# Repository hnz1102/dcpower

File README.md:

<div align="center">
  <h1><code>DC Power Unit for Breadboard</code></h1>
  
</div>

# DC Power Unit for Breadboard

This is a DC Power Unit for Breadboard based on ESP32-S3 microcontroller and AP33772S USB Power Delivery (PD) Sink Controller. It can supply power to the breadboard from USB Power Delivery (PD) Charger with support for both Standard Power Range (SPR) and Extended Power Range (EPR) modes. The output voltage can be controlled from 0v to 20V in SPR mode and up to 28V(*1) in EPR mode with step of 10mV.   
There are 2 types of adopters for the output terminal: Single positive power output terminal and dual positive/negative output terminal. It is easy to connect to the breadboard with standard 2.54mm pitch pin header. If you select the dual positive/negative output terminal adopter, the output voltage can be halved by positive and negative voltage. E.g. If you set the output voltage to 20V, you can get +10V and -10V from the positive and negative output terminal.

***1: Maximum voltage is limited to 28V by AP33772S hardware specifications. Some PD chargers may not support EPR mode or only support up to 16V/5A. Please check your PD charger specifications.**

The left image shows the single positive output terminal adopter, and the right image shows the dual positive/negative output terminal adopter.

## Key Features

- **High Power Delivery**: Up to 100W from USB PD Charger
- **Multiple Voltage Outputs**: 0V to 20V in SPR mode, 0V to 28V in EPR mode (10mV steps)
- **High Current Support**: Up to 5A when PD Charger supports EPR, but some chargers support up to 90% of the maximum current.
- **Touch Control Interface**: Front panel touch switch for voltage selection and output control
- **Precise Control**: PID controller maintains constant output voltage
- **High Accuracy Monitoring and Control**: 10mV voltage accuracy using shunt resistor and INA228 current sensor, with 1mV resolution.
- **Real-time Display**: OLED display shows voltage, current, power consumption, and temperature
- **Data Logging**: WiFi connectivity for sending measurement data to InfluxDB server
- **Web Dashboard**: Data visualization using InfluxDB dashboard
- **Safety Features**: Over Voltage Protection (OVP), Under Voltage Protection (UVP), Over Current Protection (OCP). Over Temperature Protection (OTP) does not implemented.

****Note**: If you use 21V or higher voltage, input voltage is 28v or higher, and differential voltage is over 3V and output current is over 3A, the MOSFET device is in the high consumption state and the unit temperature may rise over 80 degrees Celsius. Please be careful about the temperature. You can set the maximum temperature in the configuration file. The default value is 80 degrees Celsius. If the temperature exceeds the limit, the output will be disabled automatically. I recommend using less than 0.7A current at 21V or higher voltage. Otherwise, if you set the output voltage to 27V or higher, the temperature rise is not a problem.**

****Note**: This unit uses a micro controller and a USB PD controller. These controllers need the power to operate. Therefore, if you use a over current, the power source may be shut down by the over current protection of the PD charger. In this case, This unit cannot operate and will be turned off. Please use the current within the specification of your PD charger.**

## Hardware Components

- **ESP32-S3-WROOM-1-N16R8**: Main microcontroller
- **AP33772S**: USB Power Delivery Sink Controller with EPR support
- **INA228**: High-precision current/voltage sensor
- **SSD1331**: Color OLED display (96x64 pixels)
- **Touch Interface**: Capacitive touch sensors for user interaction
- **MOSFET Load Circuit**: Electronic load for testing and regulation

## Software Architecture

The firmware is written in Rust using the ESP-IDF framework and consists of several modules:

- `main.rs`: Main application logic and system initialization
- `usbpd.rs`: AP33772S USB-PD driver interface using the ap33772s-driver crate
- `displayctl.rs`: OLED display control and user interface
- `currentlogs.rs`: Current and voltage measurement using INA228
- `touchpad.rs`: Touch sensor interface and user input handling
- `pidcont.rs`: PID controller for voltage regulation
- `wifi.rs`: WiFi connectivity and network management
- `transfer.rs`: Data transmission to InfluxDB server
- `syslogger.rs`: System logging functionality

ap33772s-driver crate is used for USB-PD communication with the AP33772S controller. Please see the [ap33772s-driver](https://github.com/hnz1102/ap33772s-driver) for more details.

## How to Use the Unit

### Basic Operation

1. **Connection**: Connect a USB-C PD charger to the input port
2. **Power On**: The unit automatically detects the PD source and displays available power profiles
3. **Voltage Selection**: Use the touch interface to select desired output voltage
4. **Output Control**: Press the center touch position to enable/disable output
5. **Monitoring**: View real-time measurements on the OLED display

### Touch Interface Controls

- **Up/Down Touch**: Increase or decrease output voltage in 100mV steps, long press for 1V steps
- **Left/Right Touch**: Increase or decrease output voltage in 10mV steps
- **Center Touch**: Long press to toggle output ON/OFF
- **Display Information**: Shows current voltage, current, power, unit temperature, and WiFi status

**If the output is disabled due to over current, over power, or over temperature, you can clear the error message by pressing the center touch position once.**

### Safety Features

- Under Voltage Protection (UVP)
- Over Voltage Protection (OVP) 
- Over Current Protection (OCP)
- Automatic fault detection and shutdown

These protections are implemented by the AP33772S.

## Dependencies and Crates

The project uses the custom `ap33772s-driver` crate for USB-PD communication:

```toml
[dependencies]
ap33772s-driver = { version = "0.1.4", features = ["std"] }
```

Other key dependencies include:
- `esp-idf-hal` v0.45.2: ESP32 hardware abstraction
- `embedded-hal` v1.0.0: Platform-agnostic hardware interfaces
- `ssd1331` v0.3.0: OLED display driver
- `embedded-graphics` v0.7: Graphics primitives for display
- `chrono` v0.4.38: Date and time handling
- `toml-cfg` v0.1.3: Configuration file parsing

# How to build from code and Install to the unit.

Using Ubuntu 22.04.3 LTS and ESP-IDF V5.4.2

## Prerequisites
Ensure that your system meets the following requirements before proceeding with the installation:
- Operating System: Linux-based distribution
- Required Packages: git, python3, python3-pip, gcc, build-essential, curl, pkg-config, libudev-dev, libtinfo5, clang, libclang-dev, llvm-dev, udev, libssl-dev, python3.10-venv

## Installation Steps

### 1. System Update and Package Installation
Update your system and install the necessary packages using:
```bash
sudo apt update && sudo apt -y install git python3 python3-pip gcc build-essential curl pkg-config libudev-dev libtinfo5 clang libclang-dev llvm-dev udev libssl-dev python3.10-venv
```

### 2. Rust Installation
Install Rust programming language and Cargo package manager:
```bash
curl --proto '=https' --tlsv1.2 -sSf https://sh.rustup.rs | sh
```
After installation, activate Rust by sourcing the environment:
```bash
. "$HOME/.cargo/env"
```

### 3. Additional Tools Installation
Install the following Rust tools:
- ldproxy
- espup
- cargo-espflash

Use the following commands:
```bash
cargo install ldproxy
cargo install espup
cargo install cargo-espflash
```

At this time (2025-07-25), espup cannot be compiled. If you get an error, please use the following command to install the toolchain.
```bash
cargo install cargo-binstall
cargo binstall espup
```

### 4. ESP Environment Setup
Run the following command to install and update the Espressif Rust ecosystem:
```bash
espup install
espup update
```
Set up environment variables:
```bash
. ./export-esp.sh
```

### 5. Udev Rules Configuration
Configure udev rules for device permissions:
```bash
sudo sh -c 'echo "SUBSYSTEMS==\"usb\", ATTRS{idVendor}==\"303a\", ATTRS{idProduct}==\"1001\", MODE=\"0666\"" > /etc/udev/rules.d/99-esp32.rules'
sudo udevadm control --reload-rules
sudo udevadm trigger
```

### 6. Clone Repository
Clone the DC Power Unit repository:
```bash
git clone https://github.com/hnz1102/dcpower.git
cd dcpower/code
```

### 7. Setting WiFi SSID, Password, etc.
Change the following configuration file: `cfg.toml`
You have to set the following parameters: WiFi SSID, Password, InfluxDB Server IP Address, InfluxDB API Key, and InfluxDB API with your ORG.
You can get the API Key from the InfluxDB Web Console. Please see the 'How to Install the InfluxDB and Configure the Dashboard' section No.3.

```toml
[dcpowerunit]
wifi_ssid = "<Your AP SSID>"  # Set your AP SSID
wifi_psk = "<Your AP Password>" # Set your AP Password
influxdb_server = "<InfluxDB Server IP Address:Port>" # Set your InfluxDB Server IP Address and Port ex. 192.168.1.100:8086
pid_kp = "0.0000005"
pid_ki = "0.00002"
pid_kd = "0.1"
pwm_offset = "0"
pd_config_offset = "1.5"
shunt_resistance = "0.005"
shunt_temp_coefficient = "50"
max_current_limit = "5.2"
max_power_limit = "100.0"
max_temperature_limit = "75" # Set the maximum temperature limit in degrees Celsius. Default is 75 degrees.
influxdb_api_key = "<InfluxDB API KEY>" # Set your InfluxDB API Key
influxdb_api = "/api/v2/write?org=<ORG>&bucket=LOGGER&precision=ns" # Set your InfluxDB API with your ORG and BUCKET
influxdb_tag = "dcpowerunit"  # Tag for InfluxDB measurements
influxdb_measurement = "dcpowerunit" # Measurement name for InfluxDB
syslog_server = "<Syslog Server IP Address:Port>" # Set your Syslog Server IP Address and Port ex. 192.168.2.140:514
syslog_enable = "false" # Set to "true" to enable syslog
```

### 8. Build and Flash
Build the project:
```bash
cargo build --release
```

### 9. Flash the Firmware
Connect the DC Power Unit to your PC using a USB cable. Then, flash the firmware:
```bash
cargo espflash flash --release --monitor
```

If your device is not detected, power on the device and during the boot, press the `BOOT` button.
Then, run the flash command again.

### 10. Monitor the Output
After flashing the firmware, the console shows the booting messages and system initialization including:
- WiFi connection status
- AP33772S USB-PD controller initialization
- Available PDO (Power Data Object) detection
- Touch interface activation
- OLED display initialization
```bash
Chip type:         esp32s3 (revision v0.2)
Crystal frequency: 40 MHz
Flash size:        16MB
Features:          WiFi, BLE, Embedded Flash
MAC address:       80:65:99:b8:8e:90
App/part. size:    1,383,760/1,536,000 bytes, 90.09%
[00:00:00] [========================================]      14/14      0x0      Verifying... OK!                   
[00:00:00] [========================================]       1/1       0x8000   Skipped! (checksum matches)        
[00:00:15] [========================================]     864/864     0x10000  Verifying... OK!                   
[2025-09-15T07:23:38Z INFO ] Flashing has completed!
Commands:
    CTRL+R    Reset chip
    CTRL+C    Exit

ESP-ROM:esp32s3-20210327
Build:Mar 27 2021
rst:0x15 (USB_UART_CHIP_RESET),boot:0x8 (SPI_FAST_FLASH_BOOT)
Saved PC:0x40378d03
0x40378d03 - setup_priv_desc$isra$0
    at ??:??
SPIWP:0xee
mode:DIO, clock div:2
load:0x3fce2810,len:0x1564
load:0x403c8700,len:0x4
load:0x403c8704,len:0xd24
load:0x403cb700,len:0x2ed4
entry 0x403c8928
I (27) boot: ESP-IDF v5.4.2 2nd stage bootloader
I (27) boot: compile time Sep 15 2025 07:22:33
I (27) boot: Multicore bootloader
I (28) boot: chip revision: v0.2
I (30) boot: efuse block revision: v1.3
I (34) boot.esp32s3: Boot SPI Speed : 40MHz
I (38) boot.esp32s3: SPI Mode       : DIO
I (41) boot.esp32s3: SPI Flash Size : 16MB
I (45) boot: Enabling RNG early entropy source...
I (50) boot: Partition Table:
I (52) boot: ## Label            Usage          Type ST Offset   Length
I (59) boot:  0 nvs              WiFi data        01 02 00009000 00006000
I (65) boot:  1 phy_init         RF data          01 01 0000f000 00001000
I (72) boot:  2 factory          factory app      00 00 00010000 00177000
I (78) boot: End of partition table
I (81) esp_image: segment 0: paddr=00010020 vaddr=3c0f0020 size=4b244h (307780) map
I (164) esp_image: segment 1: paddr=0005b26c vaddr=3fc9c700 size=04dach ( 19884) load
I (170) esp_image: segment 2: paddr=00060020 vaddr=42000020 size=e89e8h (952808) map
I (404) esp_image: segment 3: paddr=00148a10 vaddr=3fca14ac size=00bfch (  3068) load
I (406) esp_image: segment 4: paddr=00149614 vaddr=40374000 size=186f0h (100080) load
I (437) esp_image: segment 5: paddr=00161d0c vaddr=600fe000 size=0001ch (    28) load
I (447) boot: Loaded app from partition at offset 0x10000
I (447) boot: Disabling RNG early entropy source...
I (457) octal_psram: vendor id    : 0x0d (AP)
I (457) octal_psram: dev id       : 0x02 (generation 3)
I (458) octal_psram: density      : 0x03 (64 Mbit)
I (460) octal_psram: good-die     : 0x01 (Pass)
I (464) octal_psram: Latency      : 0x01 (Fixed)
I (468) octal_psram: VCC          : 0x01 (3V)
I (472) octal_psram: SRF          : 0x01 (Fast Refresh)
I (477) octal_psram: BurstType    : 0x01 (Hybrid Wrap)
I (482) octal_psram: BurstLen     : 0x01 (32 Byte)
I (487) octal_psram: Readlatency  : 0x02 (10 cycles@Fixed)
I (492) octal_psram: DriveStrength: 0x00 (1/1)
I (497) MSPI Timing: PSRAM timing tuning index: 5
I (500) esp_psram: Found 8MB PSRAM device
I (504) esp_psram: Speed: 80MHz
I (507) cpu_start: Multicore app
I (522) cpu_start: Pro cpu start user code
I (522) cpu_start: cpu freq: 160000000 Hz
I (522) app_init: Application information:
I (522) app_init: Project name:     libespidf
I (526) app_init: App version:      100adf2
I (530) app_init: Compile time:     Sep 15 2025 07:22:02
I (535) app_init: ELF file SHA256:  000000000...
I (539) app_init: ESP-IDF:          v5.4.2
I (543) efuse_init: Min chip rev:     v0.0
I (547) efuse_init: Max chip rev:     v0.99 
I (551) efuse_init: Chip rev:         v0.2
I (555) heap_init: Initializing. RAM available for dynamic allocation:
I (561) heap_init: At 3FCA6A48 len 00042CC8 (267 KiB): RAM
I (566) heap_init: At 3FCE9710 len 00005724 (21 KiB): RAM
I (571) heap_init: At 3FCF0000 len 00008000 (32 KiB): DRAM
I (576) heap_init: At 600FE01C len 00001FCC (7 KiB): RTCRAM
I (582) esp_psram: Adding pool of 8192K of PSRAM memory to heap allocator
I (589) spi_flash: detected chip: gd
I (592) spi_flash: flash io: dio
W (595) pcnt(legacy): legacy driver is deprecated, please migrate to `driver/pulse_cnt.h`
W (602) i2c: This driver is an old driver, please migrate your application code to adapt `driver/i2c_master.h`
W (612) timer_group: legacy driver is deprecated, please migrate to `driver/gptimer.h`
I (620) sleep_gpio: Configure to isolate all GPIO pins in sleep state
I (626) sleep_gpio: Enable automatic switching of GPIO sleep configuration
I (633) main_task: Started on CPU0
I (643) esp_psram: Reserving pool of 32K of internal memory for DMA/internal allocations
I (643) main_task: Calling app_main()
I (653) gpio: GPIO[15]| InputEn: 0| OutputEn: 0| OpenDrain: 0| Pullup: 0| Pulldown: 0| Intr:0 
I (653) gpio: GPIO[16]| InputEn: 0| OutputEn: 0| OpenDrain: 0| Pullup: 0| Pulldown: 0| Intr:0 
I (663) gpio: GPIO[46]| InputEn: 0| OutputEn: 0| OpenDrain: 0| Pullup: 0| Pulldown: 0| Intr:0 
I (683) pp: pp rom version: e7ae62f
I (683) net80211: net80211 rom version: e7ae62f
I (693) wifi:wifi driver task: 3fcc44a0, prio:23, stack:6656, core=0
I (693) wifi:wifi firmware version: bea31f3
I (693) wifi:wifi certification version: v7.0
I (693) wifi:config NVS flash: disabled
I (693) wifi:config nano formatting: disabled
I (703) wifi:Init data frame dynamic rx buffer num: 32
I (703) wifi:Init static rx mgmt buffer num: 5
I (713) wifi:Init management short buffer num: 32
I (713) wifi:Init dynamic tx buffer num: 32
I (723) wifi:Init static tx FG buffer num: 2
I (723) wifi:Init static rx buffer size: 1600
I (723) wifi:Init static rx buffer num: 10
I (733) wifi:Init dynamic rx buffer num: 32
I (733) wifi_init: rx ba win: 6
I (733) wifi_init: accept mbox: 6
I (743) wifi_init: tcpip mbox: 32
I (743) wifi_init: udp mbox: 6
I (743) wifi_init: tcp mbox: 6
I (753) wifi_init: tcp tx win: 5760
I (753) wifi_init: tcp rx win: 5760
I (753) wifi_init: tcp mss: 1440
I (763) wifi_init: WiFi IRAM OP enabled
I (763) wifi_init: WiFi RX IRAM OP enabled
I (773) phy_init: phy_version 701,f4f1da3a,Mar  3 2025,15:50:10
I (803) wifi:mode : sta (80:65:99:b8:8e:90)
I (803) wifi:enable tsf
I (3313) wifi:new:<8,0>, old:<1,0>, ap:<255,255>, sta:<8,0>, prof:1, snd_ch_cfg:0x0
I (3313) wifi:state: init -> auth (0xb0)
I (3313) wifi:state: auth -> assoc (0x0)
I (3323) wifi:state: assoc -> run (0x10)
I (3333) wifi:connected with Buffalo-G-1AD0, aid = 4, channel 8, BW20, bssid = c4:3c:ea:df:1a:d0
I (3333) wifi:security: WPA2-PSK, phy: bgn, rssi: -51
I (3333) wifi:pm start, type: 1

I (3333) wifi:dp: 1, bi: 102400, li: 3, scale listen interval from 307200 us to 307200 us
I (3343) wifi:set rx beacon pti, rx_bcn_pti: 0, bcn_timeout: 25000, mt_pti: 0, mt_time: 10000
I (3423) wifi:AP's beacon interval = 102400 us, DTIM period = 1
I (5353) esp_netif_handlers: sta ip: 192.168.2.142, mask: 255.255.255.0, gw: 192.168.2.1
I (9063) wifi:<ba-add>idx:0 (ifx:0, c4:3c:ea:df:1a:d0), tid:0, ssn:3, winSize:64
I (13373) wifi:<ba-add>idx:1 (ifx:0, c4:3c:ea:df:1a:d0), tid:2, ssn:0, winSize:64
I (13383) gpio: GPIO[18]| InputEn: 0| OutputEn: 0| OpenDrain: 0| Pullup: 0| Pulldown: 0| Intr:0 
I (13393) gpio: GPIO[9]| InputEn: 0| OutputEn: 0| OpenDrain: 0| Pullup: 0| Pulldown: 0| Intr:0 
```

## How to Install the influxDB and Configure the Dashboard

### 1. Download [influxDB](https://docs.influxdata.com/influxdb/v2.7/install/?t=Linux) and Install.
```bash
$ wget https://dl.influxdata.com/influxdb/releases/influxdb2-2.7.0-amd64.deb
$ sudo dpkg -i influxdb2-2.7.0-amd64.deb
$ sudo service influxdb start
```

### 2. Configure the influxDB

```
Connect to the 'http://<influxDB installed PC Address>:8086'
```
Click `GET STARTED` and set `Username`, `Password`, `Initial Organization Name`, and `Initial Bucket Name`
|Term|Value|
|---|---|
|Username|Set login username as influxDB administrator web console|
|Password|Set login password as influxDB administrator web console|
|Initial Organization Name| Organization Name ex. ORG|
|Initial Bucket Name| LOGGER |

After set them, click `CONTINUE`.

### 3. Copy the operator API token.

You can see the operator API token on the browser. YOU WON'T BE ABLE TO SEE IT AGAIN!
If you want to get new API token, click `API Tokens` menu form `Sources` Icon, then click `GENERATE API TOKEN` and select `All access token`, click `Save`.
You can see a new API token and get it.
After copy the token, click `CONFIGURE LATER`.

### 4. Import the Dashboard Template.

Click the `Dashboard` icon, and select `Import Dashboard` from the `CREATE DASHBOARD` menu.

Drop the `influxdb/dc_power_station.json` file to `Drop a file here`, then click `IMPORT JSON AS DASHBOARD`.

You can see the `DC POWER STATION` pannel on the Dashboards page.

Click this panel, and You can see the dashboard.

If you want to customize the dashboard design, click configure mark. You can change the graph design.

## Schematic, PCB Gabar Data

There is a Schematic data in hardware directory. 

This PCB is designed by [Kicad](https://www.kicad.org/). 

## LICENSE
This source code is licensed under MIT. Other Hardware Schematic documents are licensed under CC-BY-SA V4.0.

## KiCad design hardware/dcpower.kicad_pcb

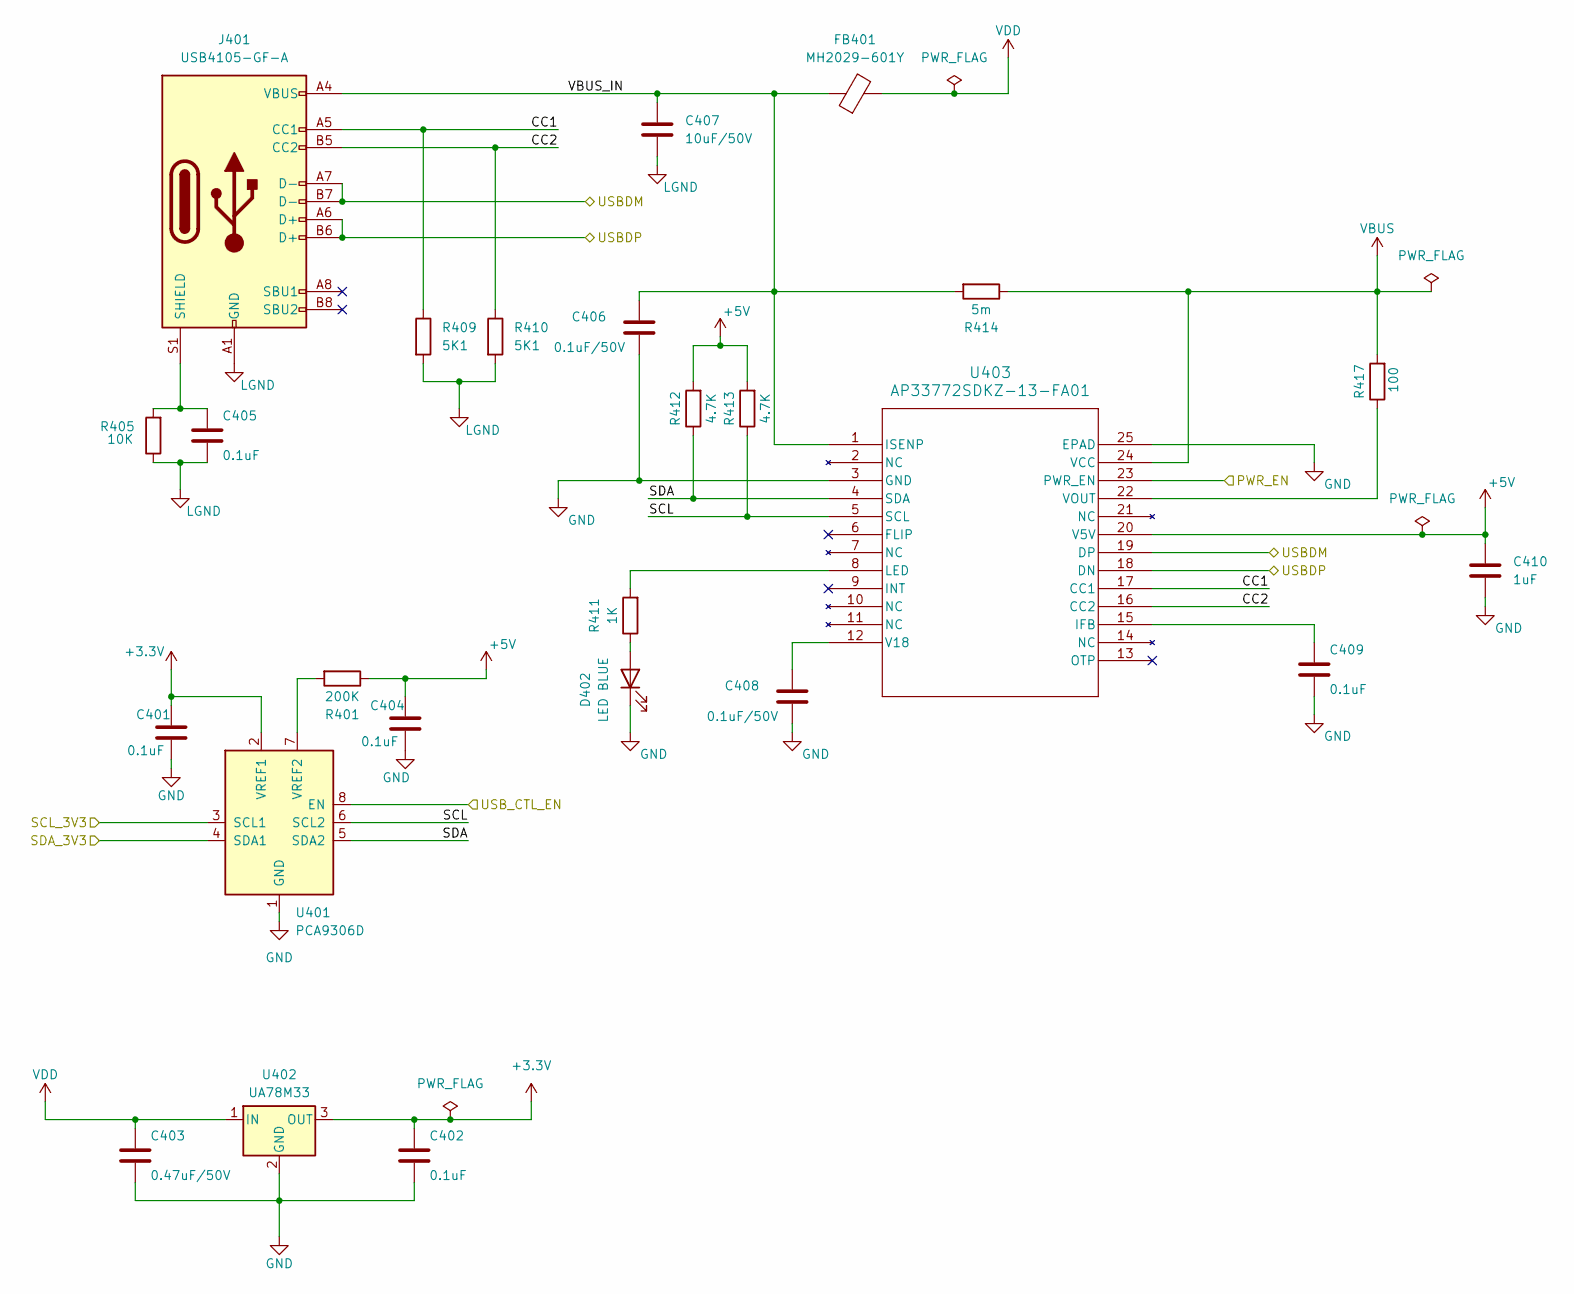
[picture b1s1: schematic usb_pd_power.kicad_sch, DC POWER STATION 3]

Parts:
C401, C402, C404, C405, C409: 0.1uF; C_0603_1608Metric; digikey 311-1343-1-ND
C403: 0.47uF/50V; C_0603_1608Metric; digikey 587-3170-1-ND
C406, C408: 0.1uF/50V; C_0603_1608Metric; digikey 311-1343-1-ND
C407: 10uF/50V; C_0805_2012Metric; digikey 490-18663-1-ND
C410: 1uF; C_0805_2012Metric; digikey 311-1365-1-ND
D402: LED BLUE; LED_0603_1608Metric; digikey 3147-B1931NB--20C007614U1930CT-ND
FB401: MH2029-601Y; L_0805_2012Metric; digikey MH2029-601YCT-ND
J401: USB4105-GF-A; USB_C_5077CR-16-SMC2-BK-TR; digikey 2073-USB4105-GF-ACT-ND
R401: 200K; R_0603_1608Metric; digikey 311-200KHRCT-ND
R405: 10K; R_0603_1608Metric; digikey 13-RC0603JR-1010KLCT-ND
R409, R410: 5K1; R_0603_1608Metric; digikey 311-5.10KHRCT-ND
R411: 1K; R_0603_1608Metric; digikey 13-RC0603JR-1010KLCT-ND
R412, R413: 4.7K; R_0603_1608Metric; digikey 311-4.70KHRCT-ND
R414: 5m; R_2512_6332Metric_Pad1.40x3.35mm_HandSolder; digikey 4506-PEWF2512D5L00Q9CT-ND
R417: 100; R_0603_1608Metric; digikey 311-100GRCT-ND
U401: PCA9306D; SSOP-8_2.95x2.8mm_P0.65mm; digikey 568-4215-1-ND
U402: UA78M33; TO-220-3_Horizontal_TabUp; digikey 296-13424-1-ND
U403: AP33772SDKZ-13-FA01; W-QFN4040-24_Type_A1_DIO; digikey 31-AP33772SDKZ-13-FA01CT-ND

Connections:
+3.3V: C401.1, C402.1, U401.2 (VREF1), U402.3 (OUT); also elsewhere on the board
+5V: C404.1, C410.1, R401.1, R412.2, R413.2, U403.20 (V5V)
/ESP32_CONT/IO21: U401.4 (SDA1); also elsewhere on the board
/ESP32_CONT/IO46: U401.8 (EN); also elsewhere on the board
/ESP32_CONT/SENSE_SCL: U401.3 (SCL1); also elsewhere on the board
/ESP32_CONT/USBDM: J401.A7 (D-), J401.B7 (D-), U403.19 (DP); also elsewhere on the board
/ESP32_CONT/USBDP: J401.A6 (D+), J401.B6 (D+), U403.18 (DN); also elsewhere on the board
/POWER_LOAD/PWR_EN: U403.23 (PWR_EN); also elsewhere on the board
/USBPDPower/CC1: J401.A5 (CC1), R409.1, U403.17 (CC1)
/USBPDPower/CC2: J401.B5 (CC2), R410.1, U403.16 (CC2)
/USBPDPower/SCL: R413.1, U401.6 (SCL2), U403.5 (SCL)
/USBPDPower/SDA: R412.1, U401.5 (SDA2), U403.4 (SDA)
/USBPDPower/VBUS_IN: C406.1, C407.1, FB401.1, J401.A4 (VBUS), J401.A9 (VBUS), J401.B4 (VBUS), J401.B9 (VBUS), R414.2, U403.1 (ISENP)
GND: C401.2, C402.2, C403.2, C404.2, C406.2, C408.2, C409.2, C410.2, D402.1 (K), U401.1 (GND), U402.2 (GND), U403.3 (GND), U403.25 (EPAD); also elsewhere on the board
LGND: C405.2, C407.2, J401.A1 (GND), J401.A12 (GND), J401.B1 (GND), J401.B12 (GND), R405.1, R409.2, R410.2; also elsewhere on the board
unnamed: D402.2 (A), R411.1
unnamed: C405.1, J401.S1 (SHIELD), R405.2
unnamed: R401.2, U401.7 (VREF2)
unnamed: C409.1, U403.15 (IFB)
unnamed: R411.2, U403.8 (LED)
unnamed: C408.1, U403.12 (V18)
unnamed: R417.1, U403.22 (VOUT)
VBUS: R414.1, R417.2, U403.24 (VCC); also elsewhere on the board
VDD: C403.1, FB401.2, U402.1 (IN); also elsewhere on the board

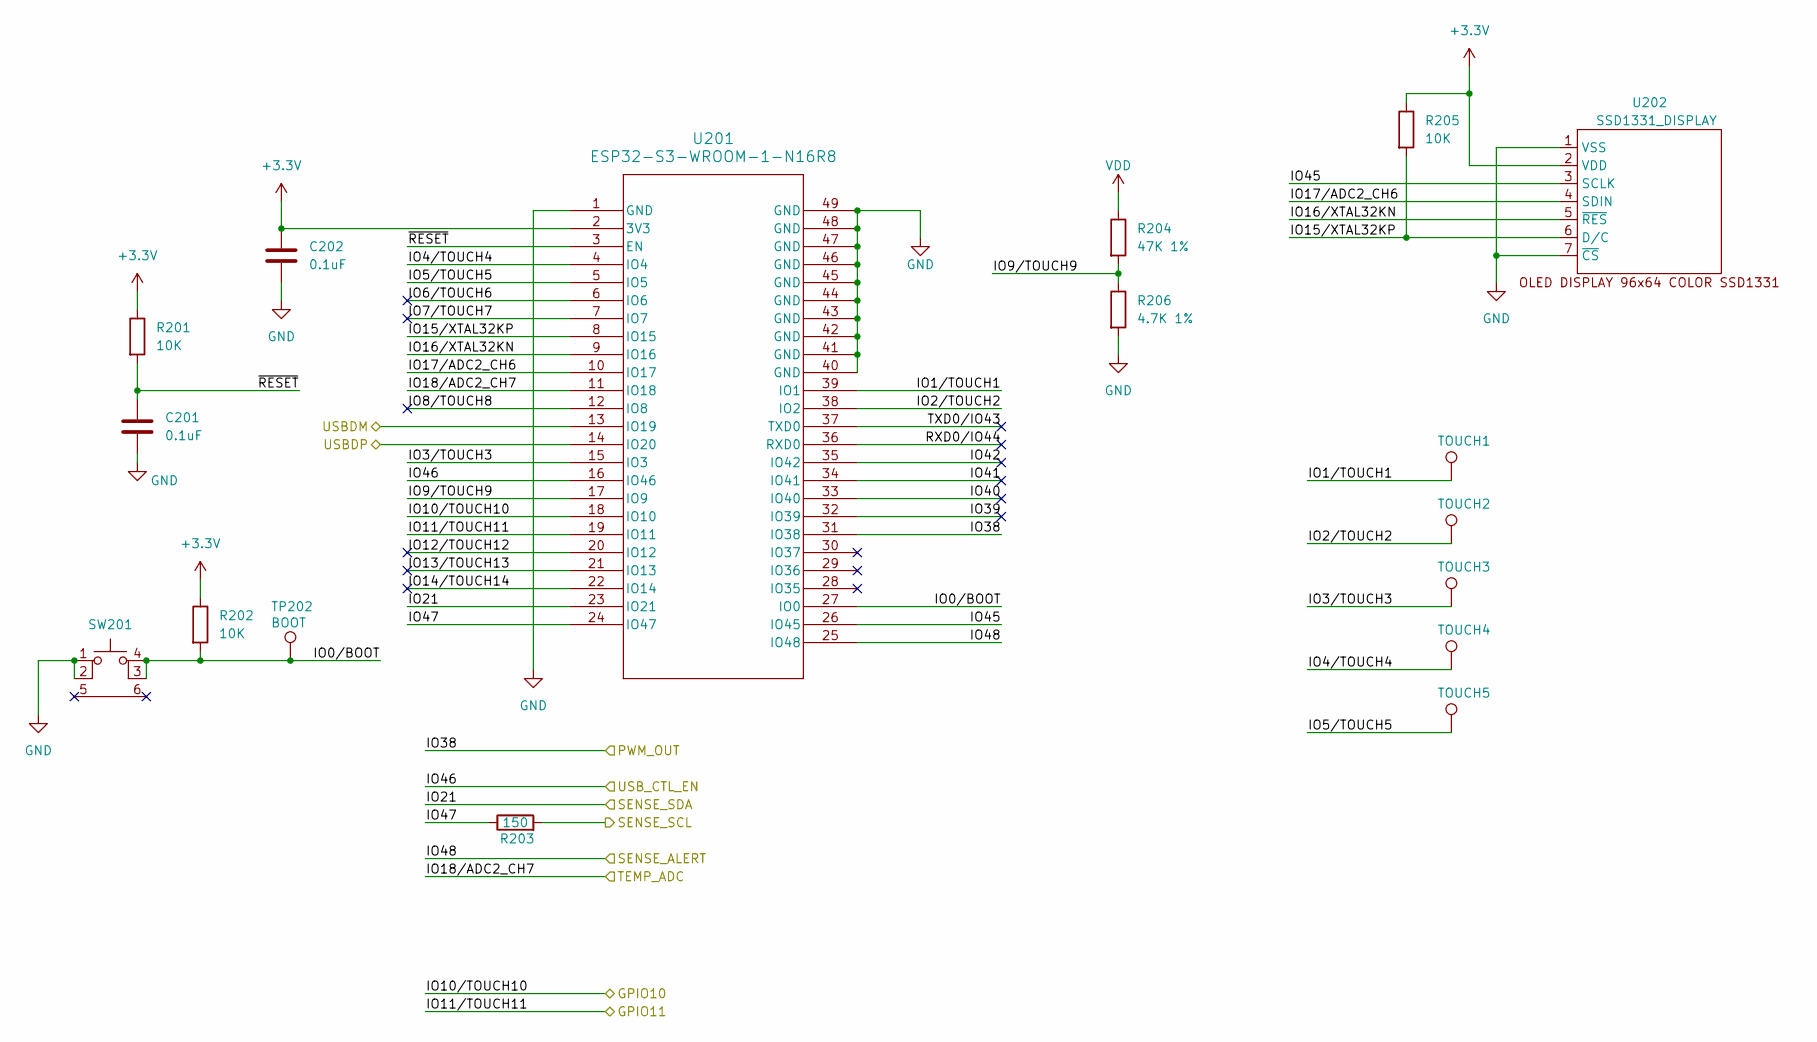
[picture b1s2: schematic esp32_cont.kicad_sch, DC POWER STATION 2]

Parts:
C201, C202: 0.1uF; C_0603_1608Metric; digikey 311-1343-1-ND
R201, R202, R205: 10K; R_0603_1608Metric; digikey 13-RC0603JR-1010KLCT-ND
R203: 150; R_0603_1608Metric; digikey 311-150GRCT-ND
R204: 47K 1%; R_0603_1608Metric; digikey 311-47.0KHRCT-ND
R206: 4.7K 1%; R_0603_1608Metric; digikey 311-4.70KHRCT-ND
SW201: 3.5x2.6 Tact SW; WS-TASV SMT Tact Switch; digikey 732-435151014824CT-ND
TP202: BOOT; TestPoint_Pad_D1.0mm
TP-PAD201: TOUCH1; TestPoint_Pad_3.2x1.6mm
TP-PAD202: TOUCH2; TestPoint_Pad_3.2x1.6mm
TP-PAD203: TOUCH3; TestPoint_Pad_3.2x1.6mm
TP-PAD204: TOUCH4; TestPoint_Pad_3.2x1.6mm
TP-PAD205: TOUCH5; TestPoint_Pad_3.2x1.6mm
U201: ESP32-S3-WROOM-1-N16R8; ESP32-S3-WROOM-1_EXP; digikey 1965-ESP32-S3-WROOM-1-N16R8CT-ND
U202: SSD1331_DISPLAY; OLED SSD1331 SPI DISPLAY; digikey 3190-DLC0095ANOB-1-ND

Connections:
+3.3V: C202.1, R201.1, R202.1, R205.1, U201.2 (3V3), U202.2 (VDD); also elsewhere on the board
/ESP32_CONT/IO0/BOOT: R202.2, SW201.3 (K), SW201.4 (A), TP202.1, U201.27 (IO0)
/ESP32_CONT/IO1/TOUCH1: TP-PAD201.1, U201.39 (IO1)
/ESP32_CONT/IO2/TOUCH2: TP-PAD202.1, U201.38 (IO2)
/ESP32_CONT/IO3/TOUCH3: TP-PAD203.1, U201.15 (IO3)
/ESP32_CONT/IO4/TOUCH4: TP-PAD204.1, U201.4 (IO4)
/ESP32_CONT/IO5/TOUCH5: TP-PAD205.1, U201.5 (IO5)
/ESP32_CONT/IO6/TOUCH6: U201.6 (IO6)
/ESP32_CONT/IO7/TOUCH7: U201.7 (IO7)
/ESP32_CONT/IO8/TOUCH8: U201.12 (IO8)
/ESP32_CONT/IO9/TOUCH9: R204.2, R206.1, U201.17 (IO9)
/ESP32_CONT/IO10/TOUCH10: U201.18 (IO10); also elsewhere on the board
/ESP32_CONT/IO11/TOUCH11: U201.19 (IO11); also elsewhere on the board
/ESP32_CONT/IO12/TOUCH12: U201.20 (IO12)
/ESP32_CONT/IO13/TOUCH13: U201.21 (IO13)
/ESP32_CONT/IO14/TOUCH14: U201.22 (IO14)
/ESP32_CONT/IO15/XTAL32KP: R205.2, U201.8 (IO15), U202.6 (D/C)
/ESP32_CONT/IO16/XTAL32KN: U201.9 (IO16), U202.5 (~RES)
/ESP32_CONT/IO17/ADC2_CH6: U201.10 (IO17), U202.4 (SDIN)
/ESP32_CONT/IO18/ADC2_CH7: U201.11 (IO18); also elsewhere on the board
/ESP32_CONT/IO21: U201.23 (IO21); also elsewhere on the board
/ESP32_CONT/IO38: U201.31 (IO38); also elsewhere on the board
/ESP32_CONT/IO39: U201.32 (IO39)
/ESP32_CONT/IO40: U201.33 (IO40)
/ESP32_CONT/IO41: U201.34 (IO41)
/ESP32_CONT/IO42: U201.35 (IO42)
/ESP32_CONT/IO45: U201.26 (IO45), U202.3 (SCLK)
/ESP32_CONT/IO46: U201.16 (IO46); also elsewhere on the board
/ESP32_CONT/IO47: R203.1, U201.24 (IO47)
/ESP32_CONT/IO48: U201.25 (IO48); also elsewhere on the board
/ESP32_CONT/RXD0/IO44: U201.36 (RXD0)
/ESP32_CONT/SENSE_SCL: R203.2; also elsewhere on the board
/ESP32_CONT/TXD0/IO43: U201.37 (TXD0)
/ESP32_CONT/USBDM: U201.13 (IO19); also elsewhere on the board
/ESP32_CONT/USBDP: U201.14 (IO20); also elsewhere on the board
/ESP32_CONT/~RESET: C201.1, R201.2, U201.3 (EN)
GND: C201.2, C202.2, R206.2, SW201.1, SW201.2, U201.1 (GND), U201.40 (GND), U201.41 (GND), U201.42 (GND), U201.43 (GND), U201.44 (GND), U201.45 (GND), U201.46 (GND), U201.47 (GND), U201.48 (GND), U201.49 (GND), U202.1 (VSS), U202.7 (~CS); also elsewhere on the board
VDD: R204.1; also elsewhere on the board

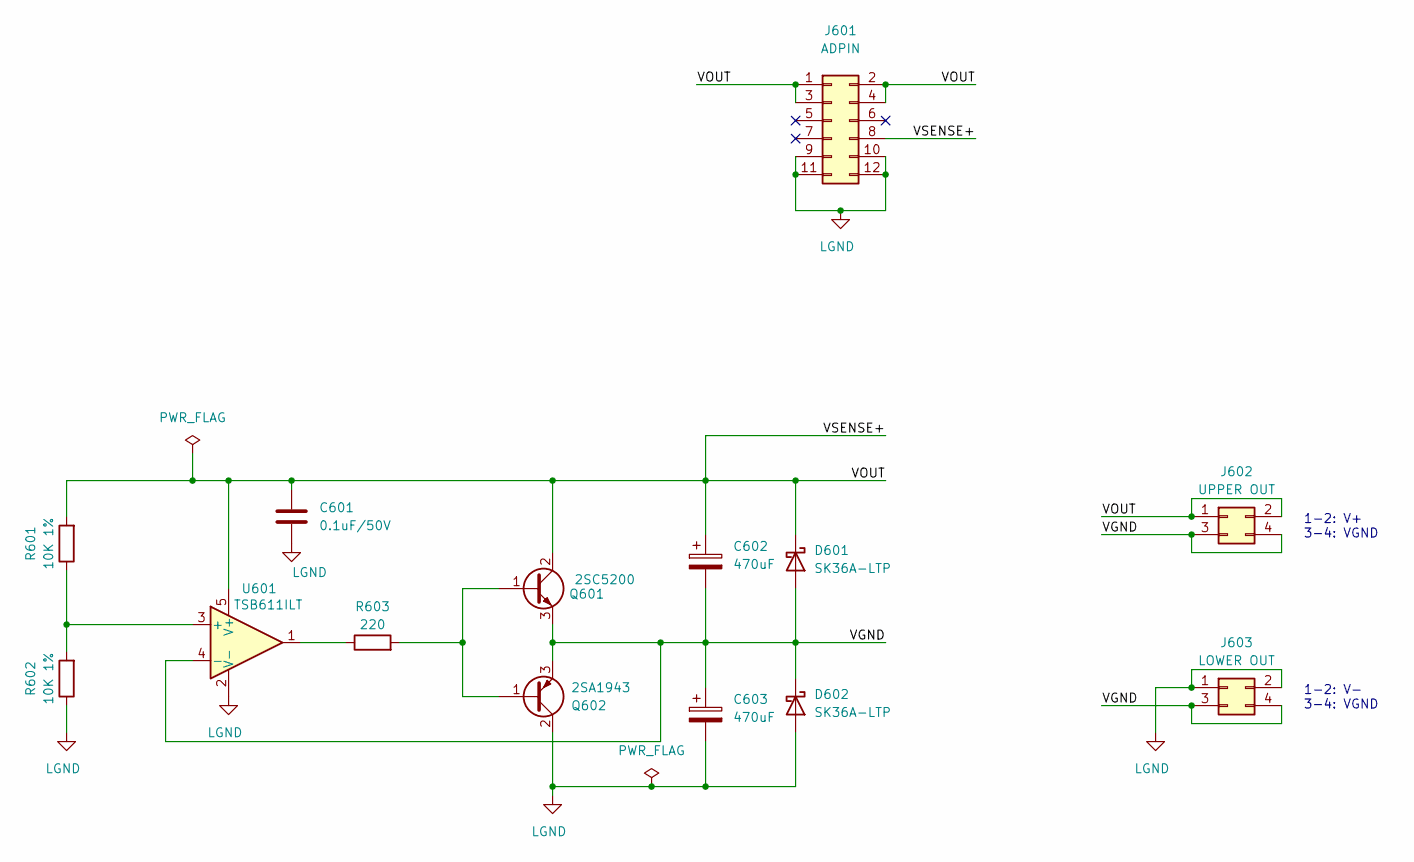
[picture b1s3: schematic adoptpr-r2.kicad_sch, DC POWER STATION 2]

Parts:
C601: 0.1uF/50V; C_0603_1608Metric; digikey 311-1343-1-ND
C602, C603: 470uF; CP_Radial_D8.0mm_P5.00mm; digikey 1189-1890-ND
D601, D602: SK36A-LTP; D_SMA; digikey SK36A-LTPMSCT-ND
J601: ADPIN; PinHeader_2x06_P2.54mm_Vertical; digikey 2057-PH2RA-12-UA-ND
J602: UPPER OUT; PinHeader_2x02_P2.54mm_Vertical; digikey 2057-PH2-04-UA-ND
J603: LOWER OUT; PinHeader_2x02_P2.54mm_Vertical; digikey 2057-PH2-04-UA-ND
Q601: 2SC5200; TO-3P-3_Horizontal_TabDown; digikey 5272-2SC5200-ND
Q602: 2SA1943; TO-3P-3_Horizontal_TabDown; digikey 5272-2SA1943-ND
R601, R602: 10K 1%; R_0603_1608Metric; digikey 311-10.0KHRCT-ND
R603: 220; R_0603_1608Metric; digikey 311-220GRCT-ND
U601: TSB611ILT; SOT-23-5; digikey 497-16082-1-ND

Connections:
/Adoptor-R2/VGND: C602.2, C603.1, D601.2 (A), D602.1 (K), J602.3, J602.4, J603.3, J603.4, Q601.3 (E), Q602.3 (E), U601.4 (-)
/Adoptor-R2/VOUT: C601.1, C602.1, D601.1 (K), J601.1, J601.2, J601.3, J601.4, J601.8, J602.1, J602.2, Q601.2 (C), R601.2, U601.5 (V+)
LGND: C601.2, C603.2, D602.2 (A), J601.9, J601.10, J601.11, J601.12, J603.1, J603.2, Q602.2 (C), R602.1, U601.2 (V-); also elsewhere on the board
unnamed: Q601.1 (B), Q602.1 (B), R603.2
unnamed: R603.1, U601.1
unnamed: R601.1, R602.2, U601.3 (+)

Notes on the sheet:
1-2: V+ 3-4: VGND
1-2: V- 3-4: VGND

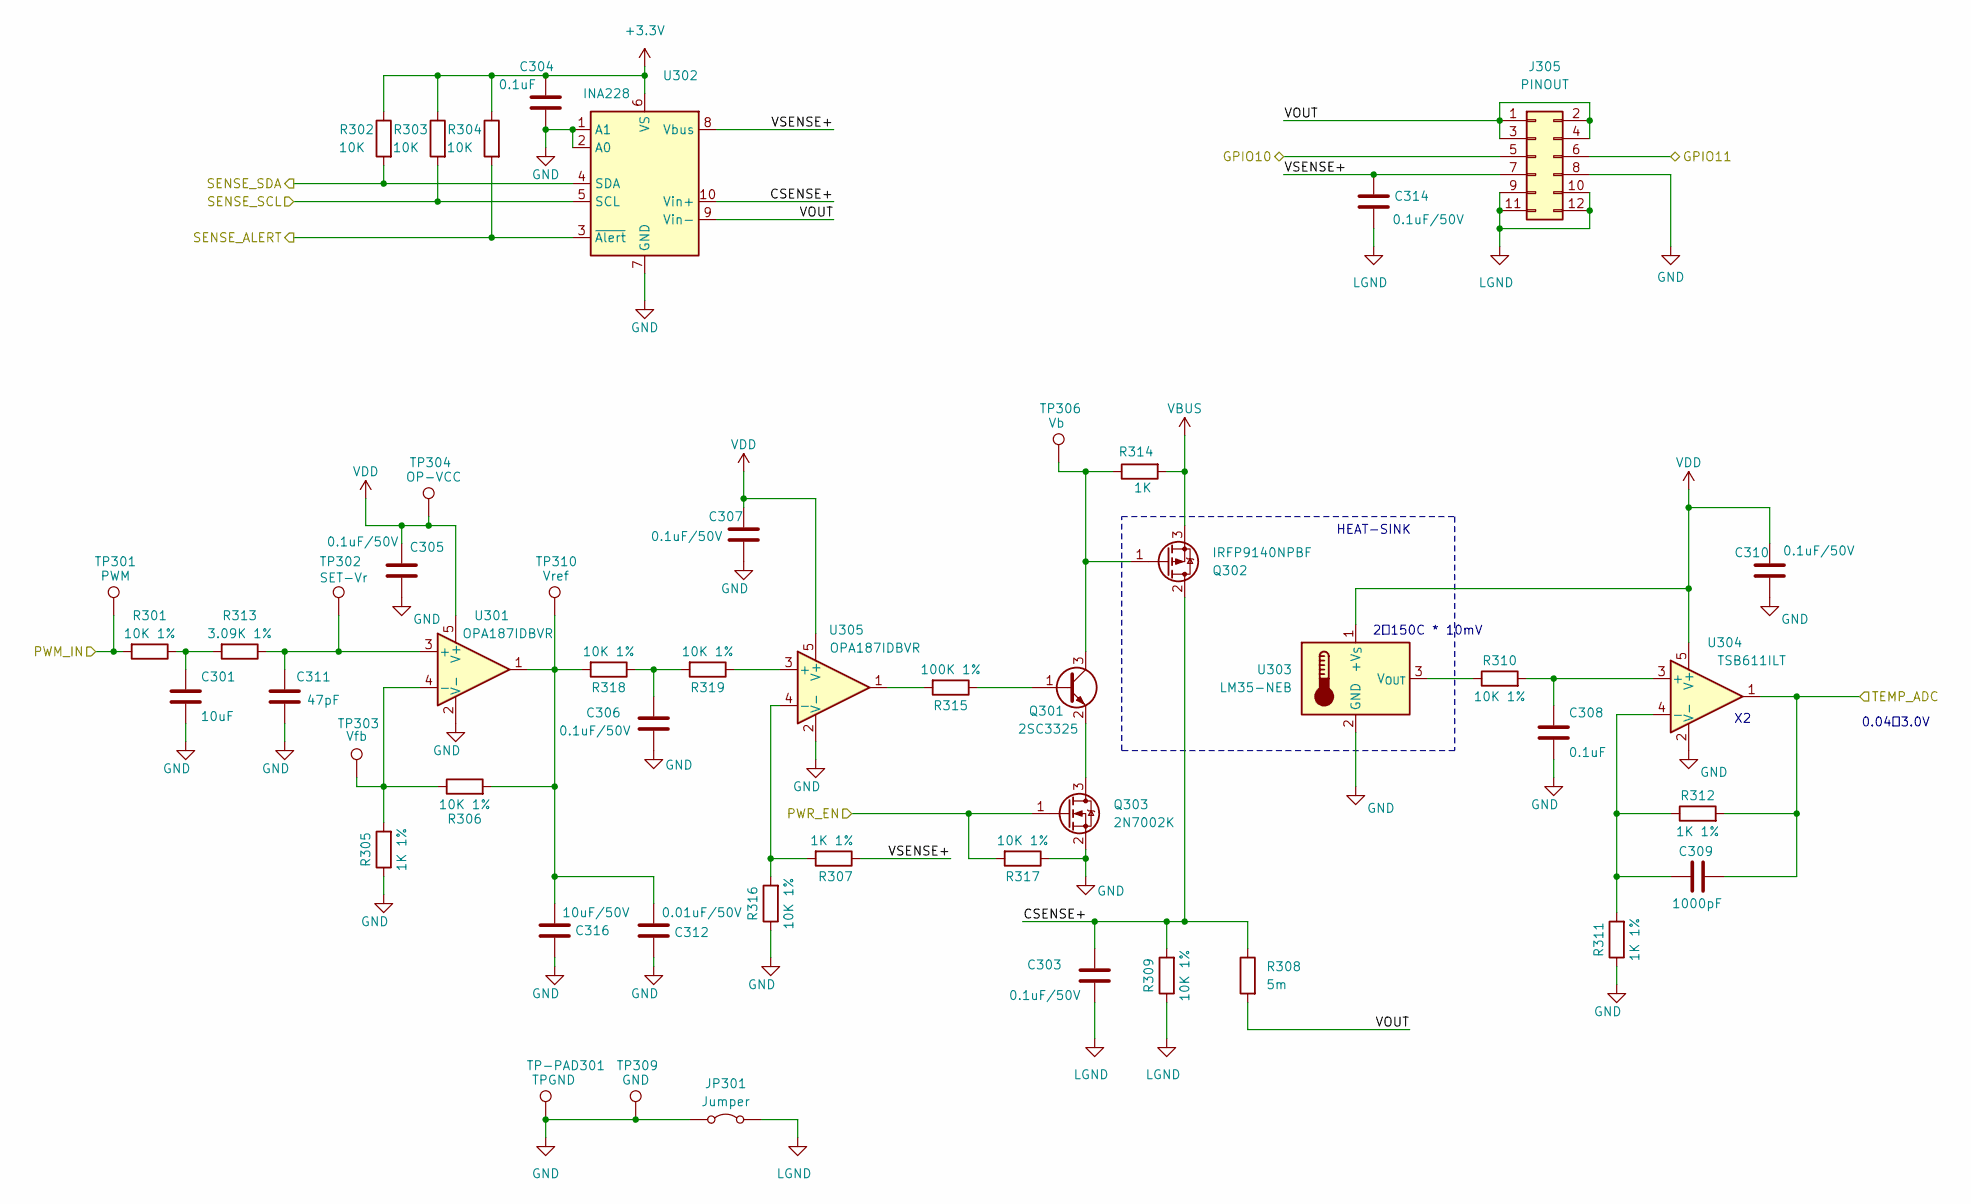
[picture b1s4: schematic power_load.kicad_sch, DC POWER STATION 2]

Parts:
C301: 10uF; C_0805_2012Metric; digikey 490-6473-1-ND
C303, C305, C306, C307, C310, C314: 0.1uF/50V; C_0603_1608Metric; digikey 311-1343-1-ND
C304, C308: 0.1uF; C_0603_1608Metric; digikey 311-1343-1-ND
C309: 1000pF; C_0603_1608Metric; digikey 311-1080-1-ND
C311: 47pF; C_0603_1608Metric; digikey 311-3980-1-ND
C312: 0.01uF/50V; C_0603_1608Metric; digikey 311-1085-1-ND
C316: 10uF/50V; C_0805_2012Metric; digikey 490-18663-1-ND
J305: PINOUT; PinHeader_2x06_P2.54mm_Vertical; digikey PPPC062LJBN-RC
JP301: Jumper; SolderJumper-2_P1.3mm_Bridged_RoundedPad1.0x1.5mm
Q301: 2SC3325; SC-59; digikey 2SC3325-YLFCT-ND
Q302: IRFP9140NPBF; TO-247-3_Horizontal_TabUp; digikey IRFP9140NPBF-ND
Q303: 2N7002K; SOT-23; digikey 2N7002KCT-ND
R301, R306, R309, R310, R316, R317, R318, R319: 10K 1%; R_0603_1608Metric; digikey 311-10.0KHRCT-ND
R302, R303, R304: 10K; R_0603_1608Metric; digikey 13-RC0603JR-1010KLCT-ND
R305, R307, R311, R312: 1K 1%; R_0603_1608Metric; digikey YAG2323CT-ND
R308: 5m; R_2512_6332Metric_Pad1.40x3.35mm_HandSolder; digikey 4506-PEWF2512D5L00Q9CT-ND
R313: 3.09K 1%; R_0603_1608Metric; digikey 311-3.09KHRCT-ND
R314: 1K; R_0603_1608Metric; digikey 13-RC0603JR-1010KLCT-ND
R315: 100K 1%; R_0603_1608Metric; digikey 311-100KHRCT-ND
TP301: PWM; TestPoint_Pad_D1.0mm
TP302: SET-Vr; TestPoint_Pad_D1.0mm
TP303: Vfb; TestPoint_Pad_D1.0mm
TP304: OP-VCC; TestPoint_Pad_D1.0mm
TP306: Vb; TestPoint_Pad_D1.0mm
TP309: GND; TestPoint_Pad_D1.0mm
TP310: Vref; TestPoint_Pad_D1.0mm
TP-PAD301: TPGND; TestPoint_Pad_3.2x1.6mm; digikey 2019-RCWCTECT-ND
U301, U305: OPA187IDBVR; SOT-23-5; digikey 296-53156-1-ND
U302: INA228; VSSOP-10_3x3mm_P0.5mm; digikey 296-INA228AIDGSRCT-ND
U303: LM35-NEB; TO-220-3_Horizontal_TabDown; digikey LM35DT/NOPB-ND
U304: TSB611ILT; SOT-23-5; digikey 497-16082-1-ND

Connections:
+3.3V: C304.1, R302.1, R303.1, R304.1, U302.6 (VS); also elsewhere on the board
/ESP32_CONT/IO10/TOUCH10: J305.5; also elsewhere on the board
/ESP32_CONT/IO11/TOUCH11: J305.6; also elsewhere on the board
/ESP32_CONT/IO18/ADC2_CH7: C309.2, R312.2, U304.1; also elsewhere on the board
/ESP32_CONT/IO21: R302.2, U302.4 (SDA); also elsewhere on the board
/ESP32_CONT/IO38: R301.2, TP301.1; also elsewhere on the board
/ESP32_CONT/IO48: R304.2, U302.3 (~Alert); also elsewhere on the board
/ESP32_CONT/SENSE_SCL: R303.2, U302.5 (SCL); also elsewhere on the board
/POWER_LOAD/CSENSE+: C303.1, Q302.2 (D), R308.1, R309.2, U302.10 (Vin+)
/POWER_LOAD/PWR_EN: Q303.1 (G), R317.2; also elsewhere on the board
/POWER_LOAD/VOUT: J305.1, J305.2, J305.3, J305.4, R308.2, U302.9 (Vin-)
/POWER_LOAD/VSENSE+: C314.1, J305.7, R307.1, U302.8 (Vbus)
GND: C301.2, C304.2, C305.2, C306.2, C307.2, C308.2, C310.2, C311.1, C312.2, C316.1, J305.8, JP301.1 (A), Q303.2 (S), R305.1, R311.1, R316.1, R317.1, TP309.1, TP-PAD301.1, U301.2 (V-), U302.1 (A1), U302.2 (A0), U302.7 (GND), U303.2 (GND), U304.2 (V-), U305.2 (V-); also elsewhere on the board
LGND: C303.2, C314.2, J305.9, J305.10, J305.11, J305.12, JP301.2 (B), R309.1; also elsewhere on the board
unnamed: C301.1, R301.1, R313.2
unnamed: C306.1, R318.1, R319.2
unnamed: C312.1, C316.2, R306.2, R318.2, TP310.1, U301.1
unnamed: Q301.1 (B), R315.1
unnamed: Q301.3 (C), Q302.1 (G), R314.1, TP306.1
unnamed: Q301.2 (E), Q303.3 (D)
unnamed: R315.2, U305.1
unnamed: C311.2, R313.1, TP302.1, U301.3 (+)
unnamed: R305.2, R306.1, TP303.1, U301.4 (-)
unnamed: R310.1, U303.3 (V_{OUT})
unnamed: C308.1, R310.2, U304.3 (+)
unnamed: C309.1, R311.2, R312.1, U304.4 (-)
unnamed: R319.1, U305.3 (+)
unnamed: R307.2, R316.2, U305.4 (-)
VBUS: Q302.3 (S), R314.2; also elsewhere on the board
VDD: C305.1, C307.1, C310.1, TP304.1, U301.5 (V+), U303.1 (+V_{S}), U304.5 (V+), U305.5 (V+); also elsewhere on the board

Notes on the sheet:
HEAT-SINK
2～150C * 10mV
0.04～3.0V

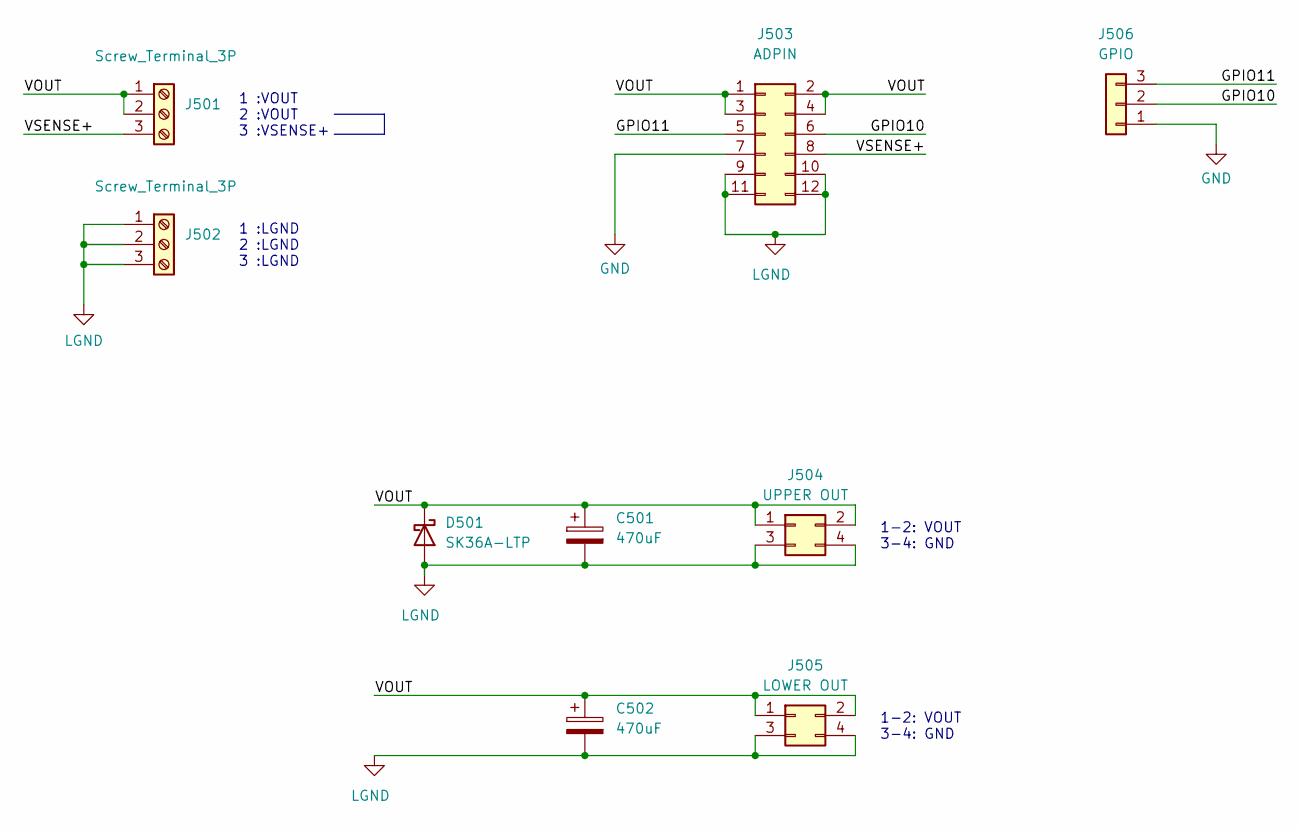
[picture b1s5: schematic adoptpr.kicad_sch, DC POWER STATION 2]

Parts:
C501, C502: 470uF; CP_Radial_D8.0mm_P5.00mm; digikey 1189-1890-ND
D501: SK36A-LTP; D_SMA; digikey SK36A-LTPMSCT-ND
J501, J502: Screw_Terminal_3P; TB112-2-2-3-E-1 Terminal Block; digikey A113321-ND
J503: ADPIN; PinHeader_2x06_P2.54mm_Vertical; digikey 2057-PH2RA-12-UA-ND
J504: UPPER OUT; PinHeader_2x02_P2.54mm_Vertical; digikey 2057-PH2-04-UA-ND
J505: LOWER OUT; PinHeader_2x02_P2.54mm_Vertical; digikey 2057-PH2-04-UA-ND
J506: GPIO; PinHeader_1x03_P2.54mm_Vertical; digikey 2057-RS1-03-G-ND

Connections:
/Adoptor-R1/GPIO10: J503.6, J506.2
/Adoptor-R1/GPIO11: J503.5, J506.3
/Adoptor-R1/VOUT: C501.1, C502.1, D501.1 (K), J501.1, J501.2, J503.1, J503.2, J503.3, J503.4, J504.1, J504.2, J505.1, J505.2
/Adoptor-R1/VSENSE+: J501.3, J503.8
GND: J503.7, J506.1; also elsewhere on the board
LGND: C501.2, C502.2, D501.2 (A), J502.1, J502.2, J502.3, J503.9, J503.10, J503.11, J503.12, J504.3, J504.4, J505.3, J505.4; also elsewhere on the board

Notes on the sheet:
1 :LGND 2 :LGND 3 :LGND
1-2: VOUT 3-4: GND
1 :VOUT 2 :VOUT 3 :VSENSE+

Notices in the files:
hardware/adoptpr-r2.kicad_sch:
(C) 2025 Hiroshi Nakajima
hardware/dcpower.kicad_pcb:
(C) 2025 HNZ USB PD SINK3 Rev.3
(C) 2025 HNZ USB PD ADAPTOR
